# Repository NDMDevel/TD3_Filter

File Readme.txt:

*************************
***** Carpeta DOCs: *****

Contiene documentacion variada, incluyendo manuales de referencia,
PCB del DAC (proyecto de Eagle) y scripts de MATLAB para diseño de
filtros y conversiones de formatos Q15.

**************************
***** Sitios utiles: *****

1- MPLAB X IDE: http://www.microchip.com/mplab/mplab-x-ide

	-> Link directo al instalador (ultima version):
	http://www.microchip.com/mplabx-ide-windows-installer
	
2- Compilador XC16: http://www.microchip.com/mplab/compilers
	
	-> Link directo al instalador de XC16 (ultima version):
	http://www.microchip.com/mplabxc16windows

3- MCC plugin: http://www.microchip.com/mplab/mplab-code-configurator

	-> Instalacion desde MPLAB X.
	
	En MPLAB X ir a: Tools->Plugins->Available Plugins. En el cuadro "Search" buscar "MCC"
	y una vez ubicado tildar el recuadro "install", luego clic en el boton "Install" (abajo a la izq.)

4- dsPIC33EP128GP502 documentacion: 
*Nota: la documentacion de modulos internos del micro (perifericos) estan abajo en la solapa "Documents", seccion "Reference Manual".

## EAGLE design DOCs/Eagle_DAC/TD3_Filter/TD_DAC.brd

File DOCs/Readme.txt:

Sitios utiles:

1- MPLAB X IDE: http://www.microchip.com/mplab/mplab-x-ide

	-> Link directo al instalador (ultima version):
	http://www.microchip.com/mplabx-ide-windows-installer
	
2- Compilador XC16: http://www.microchip.com/mplab/compilers
	
	-> Link directo al instalador de XC16 (ultima version):
	http://www.microchip.com/mplabxc16windows

3- MCC plugin: http://www.microchip.com/mplab/mplab-code-configurator

	-> Instalacion desde MPLAB X.
	
	En MPLAB X ir a: Tools->Plugins->Available Plugins. En el cuadro "Search" buscar "MCC"
	y una vez ubicado tildar el recuadro "install", luego clic en el boton "Install" (abajo a la izq.)

4- dsPIC33EP128GP502 documentacion: 
*Nota: la documentacion de modulos internos del micro (perifericos) estan abajo en la solapa "Documents", seccion "Reference Manual".

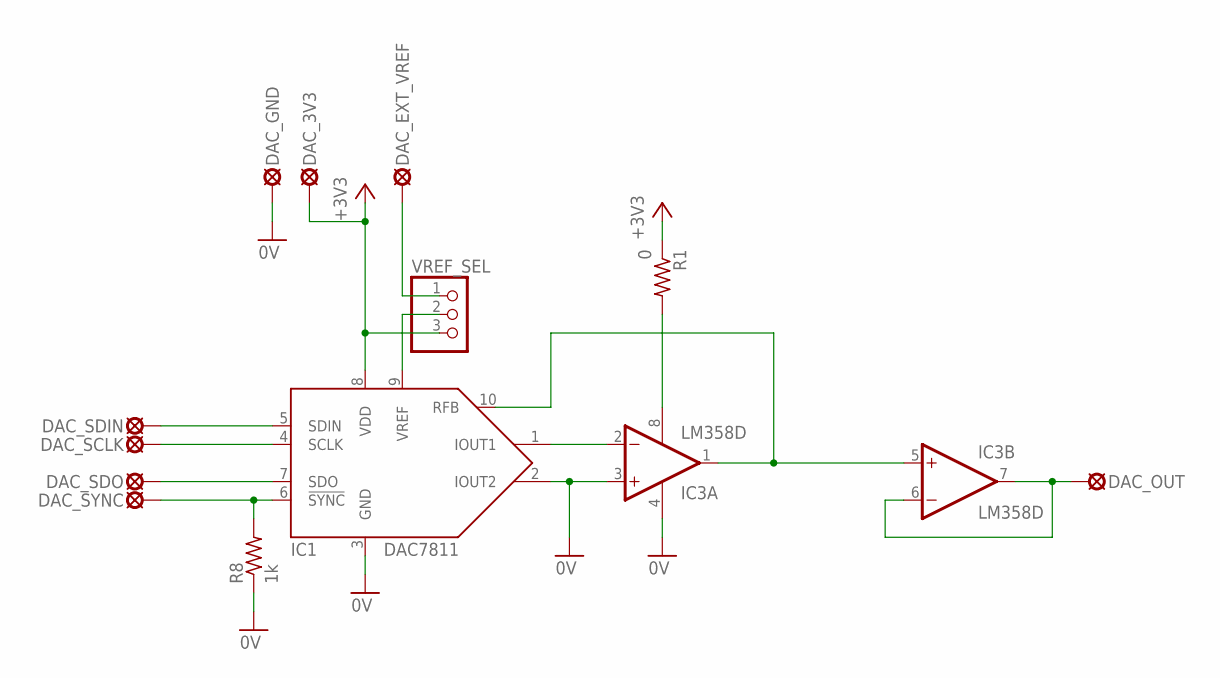
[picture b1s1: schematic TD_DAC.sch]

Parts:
DAC_3V3: LSP10
DAC_EXT_VREF: LSP10
DAC_GND: LSP10
DAC_OUT: LSP10
DAC_SCLK: LSP10
DAC_SDIN: LSP10
DAC_SDO: LSP10
DAC_SYNC: LSP10
IC1: DAC7811; S-PDSO-G10
IC3: LM358D; SO08
R1: 0; R1206
R8: 1k; R0805
VREF_SEL: PINHD-1X3; 1X03

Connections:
0V: DAC_GND.MP, IC1.2 (IOUT2), IC1.3 (GND), IC3.3 (+IN), IC3.4 (V-), R8.1
+3V3: DAC_3V3.MP, IC1.8 (VDD), R1.1, VREF_SEL.3
MCU_SCLK: DAC_SCLK.MP, IC1.4 (SCLK)
MCU_SDO: DAC_SDIN.MP, IC1.5 (SDIN)
unnamed: IC1.1 (IOUT1), IC3.2 (-IN)
unnamed: DAC_OUT.MP, IC3.6 (-IN), IC3.7 (OUT)
unnamed: IC1.9 (VREF), VREF_SEL.2
unnamed: DAC_EXT_VREF.MP, VREF_SEL.1
unnamed: DAC_SYNC.MP, IC1.6 (!SYNC!), R8.2
unnamed: IC1.10 (RFB), IC3.1 (OUT), IC3.5 (+IN)
unnamed: IC3.8 (V+), R1.2
unnamed: DAC_SDO.MP, IC1.7 (SDO)

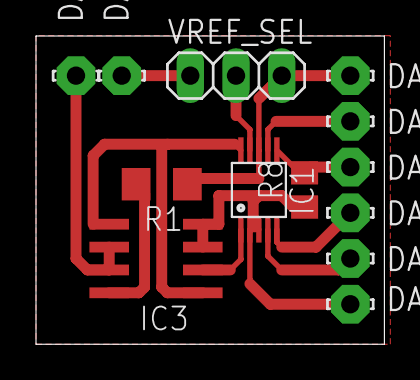
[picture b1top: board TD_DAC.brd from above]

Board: 2 copper layers, 19.4 x 17.1 mm, 13 parts (0 on the bottom side), 12 nets.

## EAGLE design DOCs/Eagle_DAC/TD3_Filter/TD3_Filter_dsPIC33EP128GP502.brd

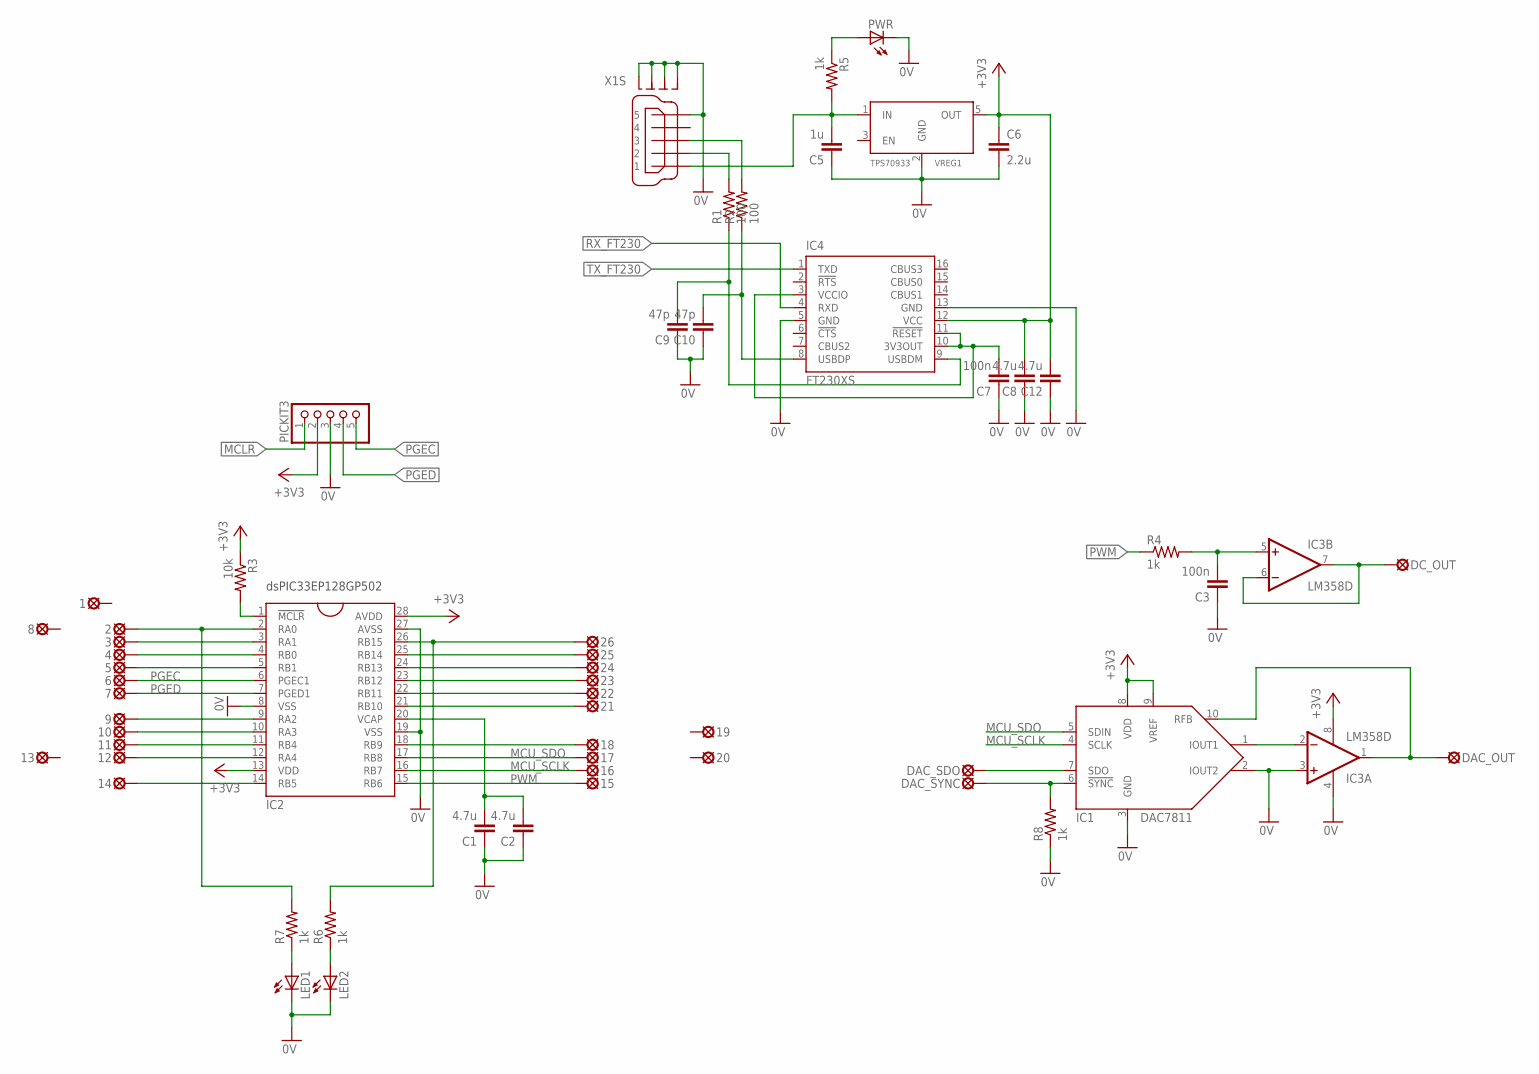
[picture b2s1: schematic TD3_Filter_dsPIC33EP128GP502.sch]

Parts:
1, 2, 3, 4, 5, 6, 7, 8, 9, 10, 11, 12, 13, 14, 15, 16, 17, 18, 19, 20, 21, 22, 23, 24, 25, 26: LSP10
C1, C2, C8, C12: 4.7u; C1206
C3, C7: 100n; C1206
C5: 1u; C1206
C6: 2.2u; C1206
C9, C10: 47p; C1206
DAC_OUT: LSP10
DAC_SDO: LSP10
DAC_SYNC: LSP10
DC_OUT: LSP10
IC1: DAC7811; S-PDSO-G10
IC2: DSPIC33EP128GP502; DIL28
IC3: LM358D; SO08
IC4: FT230XS; SSOP16
LED1, LED2: LED3MM
PICKIT3: PINHD-1X5; 1X05
PWR: LED3MM
R1: 100; R0805
R2: 100; R1206
R3: 10k; R0805
R4, R5, R6, R7, R8: 1k; R0805
VREG1: TPS70933
X1: MINI-USB_SHIELD5P4-32005-400; 32005-400

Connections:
0V: C1.1, C2.1, C3.1, C5.1, C6.2, C7.1, C8.1, C9.1, C10.1, C12.1, IC1.2 (IOUT2), IC1.3 (GND), IC2.8 (VSS), IC2.19 (VSS), IC2.27 (AVSS), IC3.3 (+IN), IC3.4 (V-), IC4.5 (GND), IC4.13 (GND), LED1.K (C), LED2.K (C), PICKIT3.3, PWR.K (C), R8.1, VREG1.2 (GND), X1.5, X1.M1 (S1), X1.M2 (S2), X1.M3 (S3), X1.M4 (S4)
!MCLR!: PICKIT3.1
+3V3: C6.1, C8.2, C12.2, IC1.8 (VDD), IC1.9 (VREF), IC2.13 (VDD), IC2.28 (AVDD), IC3.8 (V+), IC4.12 (VCC), PICKIT3.2, R3.1, VREG1.5 (OUT)
MCU_SCLK: 16.MP, IC1.4 (SCLK), IC2.16 (RB7)
MCU_SDO: 17.MP, IC1.5 (SDIN), IC2.17 (RB8)
unnamed: IC1.1 (IOUT1), IC3.2 (-IN)
unnamed: C3.2, IC3.5 (+IN), R4.2
unnamed: PWR.A, R5.1
unnamed: IC2.1 (!MCLR!), R3.2
unnamed: DAC_SYNC.MP, IC1.6 (!SYNC!), R8.2
unnamed: C7.2, IC4.3 (VCCIO), IC4.10 (3V3OUT), IC4.11 (!RESET)
unnamed: R2.2, X1.3
unnamed: C1.2, C2.2, IC2.20 (VCAP)
unnamed: DAC_SDO.MP, IC1.7 (SDO)
unnamed: C10.2, IC4.8 (USBDP), R2.1
unnamed: R1.2, X1.2
unnamed: C9.2, IC4.9 (USBDM), R1.1
unnamed: DAC_OUT.MP, IC1.10 (RFB), IC3.1 (OUT)
unnamed: DC_OUT.MP, IC3.6 (-IN), IC3.7 (OUT)
unnamed: 3.MP, IC2.3 (RA1)
unnamed: 4.MP, IC2.4 (RB0)
unnamed: 5.MP, IC2.5 (RB1)
unnamed: 9.MP, IC2.9 (RA2)
unnamed: 10.MP, IC2.10 (RA3)
unnamed: 11.MP, IC2.11 (RB4)
unnamed: 12.MP, IC2.12 (RA4)
unnamed: 14.MP, IC2.14 (RB5)
unnamed: 22.MP, IC2.22 (RB11)
unnamed: 18.MP, IC2.18 (RB9)
unnamed: 21.MP, IC2.21 (RB10)
unnamed: 23.MP, IC2.23 (RB12)
unnamed: 24.MP, IC2.24 (RB13)
unnamed: 25.MP, IC2.25 (RB14)
unnamed: LED2.A, R6.1
unnamed: LED1.A, R7.1
unnamed: 2.MP, IC2.2 (RA0), R7.2
unnamed: C5.2, R5.2, VREG1.1 (IN), X1.1
unnamed: 26.MP, IC2.26 (RB15), R6.2
PGEC: 6.MP, IC2.6 (PGEC1), PICKIT3.5
PGED: 7.MP, IC2.7 (PGED1), PICKIT3.4
PWM: 15.MP, IC2.15 (RB6), R4.1
RX_FT230: IC4.4 (RXD)
TX_FT230: IC4.1 (TXD)

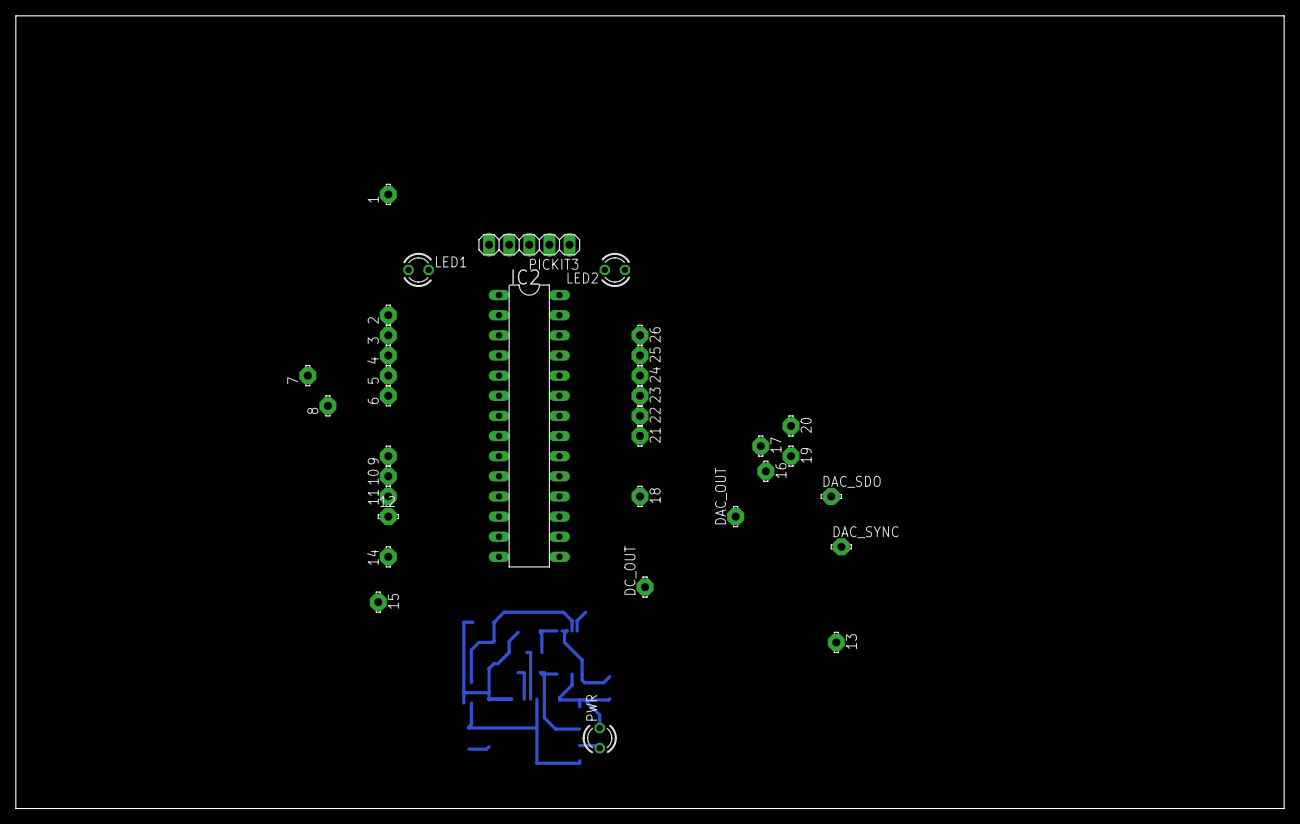
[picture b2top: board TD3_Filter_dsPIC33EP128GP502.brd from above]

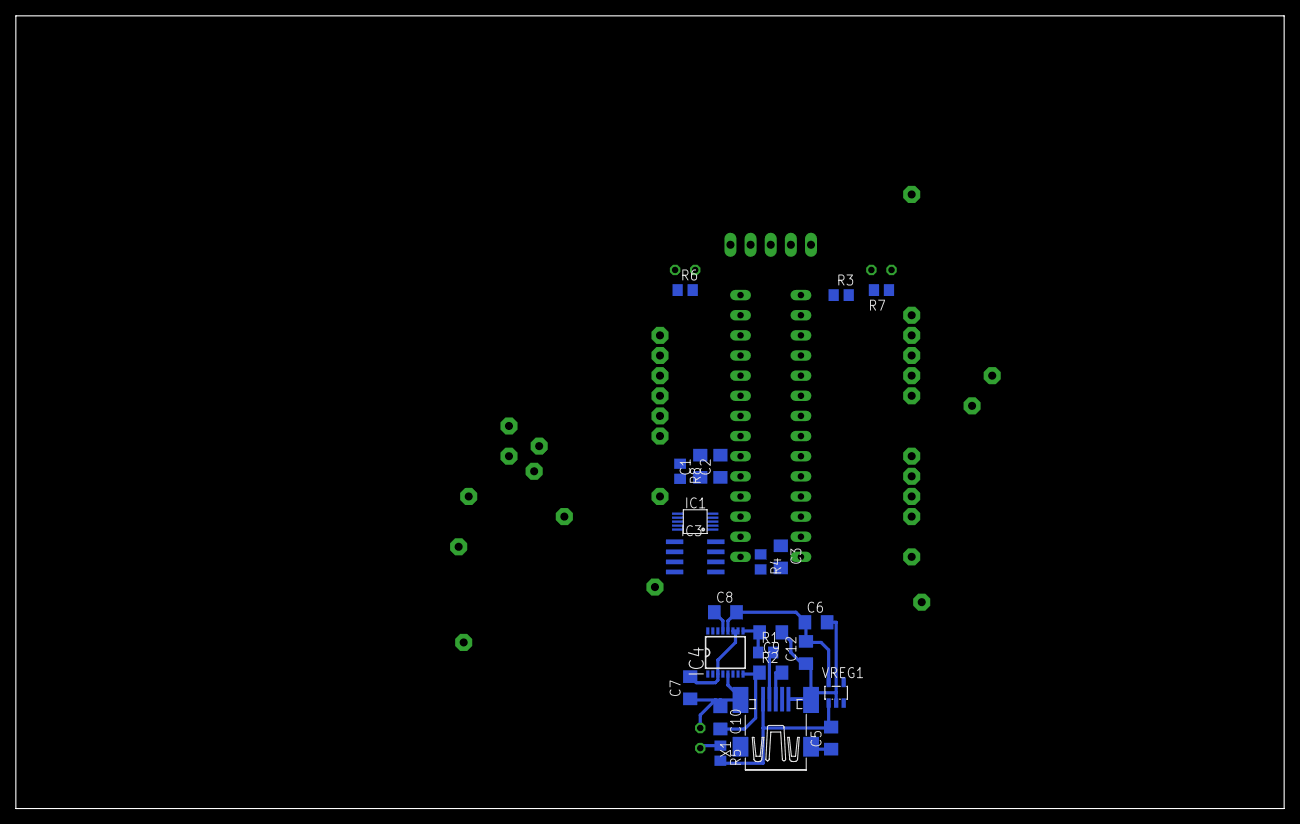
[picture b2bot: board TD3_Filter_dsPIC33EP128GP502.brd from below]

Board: 2 copper layers, 160.0 x 100.0 mm, 58 parts (23 on the bottom side), 40 nets.

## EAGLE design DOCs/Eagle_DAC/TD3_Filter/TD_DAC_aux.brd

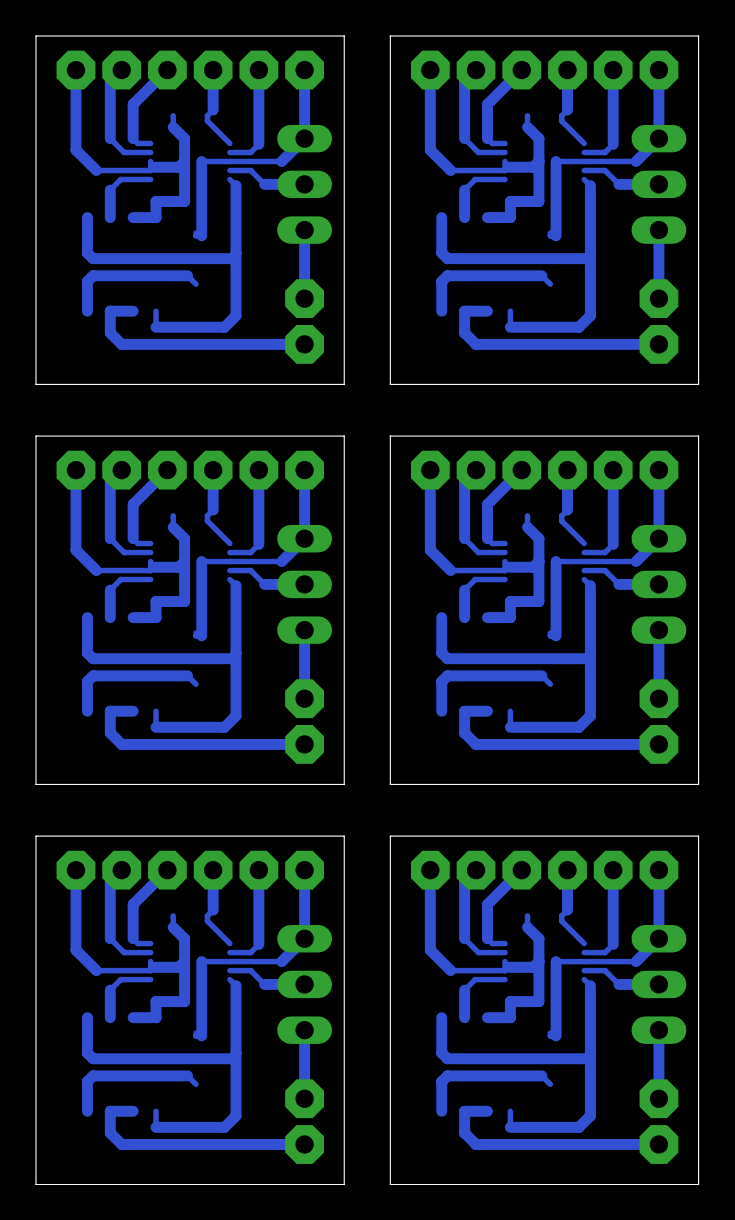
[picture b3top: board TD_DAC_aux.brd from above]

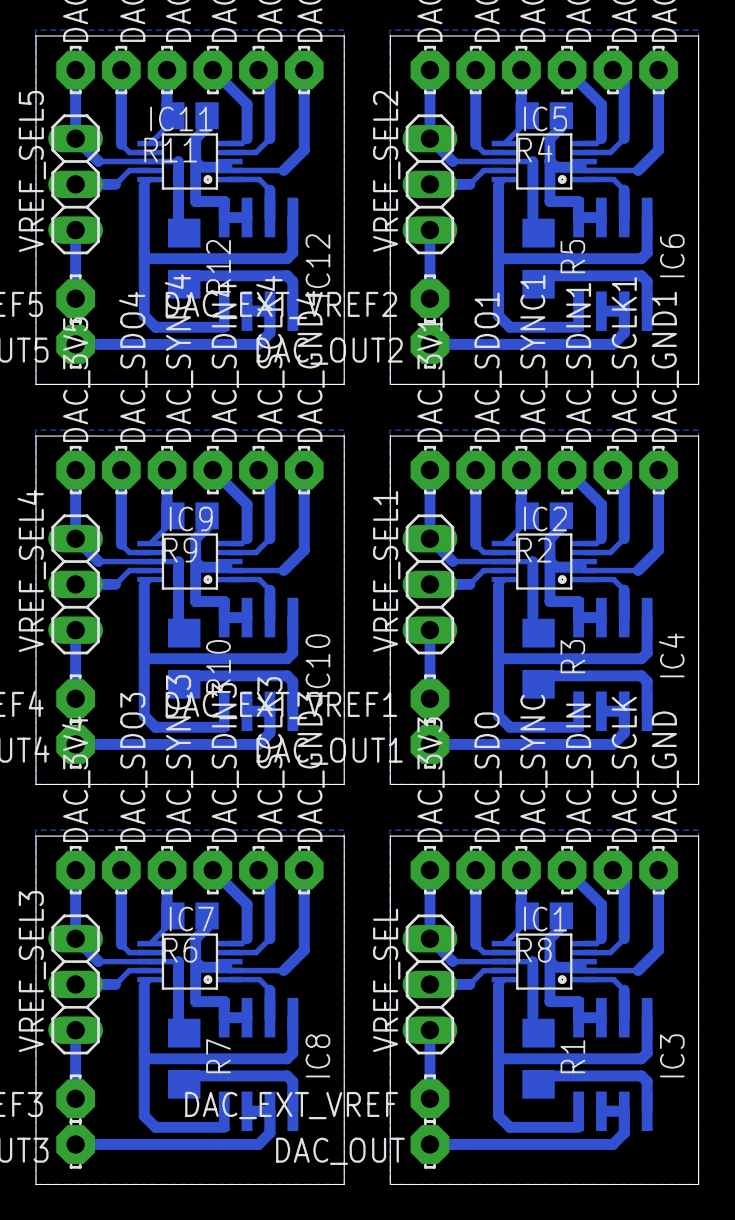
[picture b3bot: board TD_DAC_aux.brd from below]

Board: 2 copper layers, 36.8 x 63.8 mm, 78 parts (78 on the bottom side), 72 nets.

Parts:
DAC_3V1, DAC_3V2, DAC_3V3, DAC_3V4, DAC_3V5, DAC_3V6: LSP10
DAC_EXT_VREF, DAC_EXT_VREF1, DAC_EXT_VREF2, DAC_EXT_VREF3, DAC_EXT_VREF4, DAC_EXT_VREF5: LSP10
DAC_GND, DAC_GND1, DAC_GND2, DAC_GND3, DAC_GND4, DAC_GND5: LSP10
DAC_OUT, DAC_OUT1, DAC_OUT2, DAC_OUT3, DAC_OUT4, DAC_OUT5: LSP10
DAC_SCLK, DAC_SCLK1, DAC_SCLK2, DAC_SCLK3, DAC_SCLK4, DAC_SCLK5: LSP10
DAC_SDIN, DAC_SDIN1, DAC_SDIN2, DAC_SDIN3, DAC_SDIN4, DAC_SDIN5: LSP10
DAC_SDO, DAC_SDO1, DAC_SDO2, DAC_SDO3, DAC_SDO4, DAC_SDO5: LSP10
DAC_SYNC, DAC_SYNC1, DAC_SYNC2, DAC_SYNC3, DAC_SYNC4, DAC_SYNC5: LSP10
IC1, IC2, IC5, IC7, IC9, IC11: S-PDSO-G10
IC3, IC4, IC6, IC8, IC10, IC12: LM358D; SO08
R1, R3, R5, R7, R10, R12: 0; R1206
R2, R4, R6, R8, R9, R11: 1k; R0805
VREF_SEL, VREF_SEL1, VREF_SEL2, VREF_SEL3, VREF_SEL4, VREF_SEL5: 1X03

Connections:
0V: DAC_GND.MP, IC1.2, IC1.3, IC3.3, IC3.4, R8.1
0V1: DAC_GND1.MP, IC2.2, IC2.3, IC4.3, IC4.4, R2.1
0V2: DAC_GND2.MP, IC5.2, IC5.3, IC6.3, IC6.4, R4.1
0V3: DAC_GND3.MP, IC7.2, IC7.3, IC8.3, IC8.4, R6.1
0V4: DAC_GND4.MP, IC9.2, IC9.3, IC10.3, IC10.4, R9.1
0V5: DAC_GND5.MP, IC11.2, IC11.3, IC12.3, IC12.4, R11.1
+3V1: DAC_3V1.MP, IC2.8, R3.1, VREF_SEL1.3
+3V2: DAC_3V2.MP, IC5.8, R5.1, VREF_SEL2.3
+3V3: DAC_3V3.MP, IC1.8, R1.1, VREF_SEL.3
+3V4: DAC_3V4.MP, IC7.8, R7.1, VREF_SEL3.3
+3V5: DAC_3V5.MP, IC9.8, R10.1, VREF_SEL4.3
+3V6: DAC_3V6.MP, IC11.8, R12.1, VREF_SEL5.3
MCU_SCLK: DAC_SCLK.MP, IC1.4
MCU_SCLK1: DAC_SCLK1.MP, IC2.4
MCU_SCLK2: DAC_SCLK2.MP, IC5.4
MCU_SCLK3: DAC_SCLK3.MP, IC7.4
MCU_SCLK4: DAC_SCLK4.MP, IC9.4
MCU_SCLK5: DAC_SCLK5.MP, IC11.4
MCU_SDO: DAC_SDIN.MP, IC1.5
MCU_SDO1: DAC_SDIN1.MP, IC2.5
MCU_SDO2: DAC_SDIN2.MP, IC5.5
MCU_SDO3: DAC_SDIN3.MP, IC7.5
MCU_SDO4: DAC_SDIN4.MP, IC9.5
MCU_SDO5: DAC_SDIN5.MP, IC11.5
unnamed: IC1.1, IC3.2
unnamed: DAC_OUT.MP, IC3.6, IC3.7
unnamed: IC1.9, VREF_SEL.2
unnamed: DAC_EXT_VREF.MP, VREF_SEL.1
unnamed: DAC_SYNC.MP, IC1.6, R8.2
unnamed: IC1.10, IC3.1, IC3.5
unnamed: IC3.8, R1.2
unnamed: IC2.1, IC4.2
unnamed: DAC_SDO.MP, IC1.7
unnamed: DAC_SYNC1.MP, IC2.6, R2.2
unnamed: DAC_SDO1.MP, IC2.7
unnamed: DAC_OUT1.MP, IC4.6, IC4.7
unnamed: IC2.9, VREF_SEL1.2
unnamed: DAC_EXT_VREF1.MP, VREF_SEL1.1
unnamed: IC2.10, IC4.1, IC4.5
unnamed: IC4.8, R3.2
unnamed: IC5.1, IC6.2
unnamed: DAC_SYNC2.MP, IC5.6, R4.2
unnamed: DAC_SDO2.MP, IC5.7
unnamed: DAC_OUT2.MP, IC6.6, IC6.7
unnamed: IC5.9, VREF_SEL2.2
unnamed: DAC_EXT_VREF2.MP, VREF_SEL2.1
unnamed: IC5.10, IC6.1, IC6.5
unnamed: IC6.8, R5.2
unnamed: IC7.1, IC8.2
unnamed: DAC_SYNC3.MP, IC7.6, R6.2
unnamed: DAC_SDO3.MP, IC7.7
unnamed: DAC_OUT3.MP, IC8.6, IC8.7
unnamed: IC7.9, VREF_SEL3.2
unnamed: DAC_EXT_VREF3.MP, VREF_SEL3.1
unnamed: IC7.10, IC8.1, IC8.5
unnamed: IC8.8, R7.2
unnamed: IC9.1, IC10.2
unnamed: DAC_SYNC4.MP, IC9.6, R9.2
unnamed: DAC_SDO4.MP, IC9.7
unnamed: DAC_OUT4.MP, IC10.6, IC10.7
unnamed: IC9.9, VREF_SEL4.2
unnamed: DAC_EXT_VREF4.MP, VREF_SEL4.1
unnamed: IC9.10, IC10.1, IC10.5
unnamed: IC10.8, R10.2
unnamed: IC11.1, IC12.2
unnamed: DAC_SYNC5.MP, IC11.6, R11.2
unnamed: DAC_SDO5.MP, IC11.7
unnamed: DAC_OUT5.MP, IC12.6, IC12.7
unnamed: IC11.9, VREF_SEL5.2
unnamed: DAC_EXT_VREF5.MP, VREF_SEL5.1
unnamed: IC11.10, IC12.1, IC12.5
unnamed: IC12.8, R12.2

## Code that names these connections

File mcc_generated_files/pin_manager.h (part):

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*/
/**
  @Summary
    Sets the GPIO pin, RA0, high using LATA0.

  @Description
    Sets the GPIO pin, RA0, high using LATA0.

  @Preconditions
    The RA0 must be set to an output.
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#define channel_AN0_SetHigh()          _LATA0 = 1
/**
  @Summary
    Sets the GPIO pin, RA0, low using LATA0.

  @Description
    Sets the GPIO pin, RA0, low using LATA0.

  @Preconditions
    The RA0 must be set to an output.
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#define channel_AN0_SetLow()           _LATA0 = 0
/**
  @Summary
    Toggles the GPIO pin, RA0, using LATA0.

  @Description
    Toggles the GPIO pin, RA0, using LATA0.

  @Preconditions
    The RA0 must be set to an output.
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#define channel_AN0_Toggle()           _LATA0 ^= 1
/**
  @Summary
    Reads the value of the GPIO pin, RA0.

  @Description
    Reads the value of the GPIO pin, RA0.

  @Preconditions
    None.
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    </code>

*/
#define channel_AN0_GetValue()         _RA0
/**
  @Summary
    Configures the GPIO pin, RA0, as an input.

  @Description
    Configures the GPIO pin, RA0, as an input.

  @Preconditions
    None.
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#define channel_AN0_SetDigitalInput()  _TRISA0 = 1
/**
  @Summary
    Configures the GPIO pin, RA0, as an output.

  @Description
    Configures the GPIO pin, RA0, as an output.

  @Preconditions
    None.
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#define channel_AN0_SetDigitalOutput() _TRISA0 = 0
/**
  @Summary
    Sets the GPIO pin, RB0, high using LATB0.

  @Description
    Sets the GPIO pin, RB0, high using LATB0.

  @Preconditions
    The RB0 must be set to an output.
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#define SS1_SetHigh()          _LATB0 = 1
/**
  @Summary
    Sets the GPIO pin, RB0, low using LATB0.

  @Description
    Sets the GPIO pin, RB0, low using LATB0.

  @Preconditions
    The RB0 must be set to an output.
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#define SS1_SetLow()           _LATB0 = 0
/**
  @Summary
    Toggles the GPIO pin, RB0, using LATB0.

  @Description
    Toggles the GPIO pin, RB0, using LATB0.

  @Preconditions
    The RB0 must be set to an output.
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#define SS1_Toggle()           _LATB0 ^= 1
/**
  @Summary
    Reads the value of the GPIO pin, RB0.

  @Description
    Reads the value of the GPIO pin, RB0.

  @Preconditions
    None.
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    </code>

*/
#define SS1_GetValue()         _RB0
/**
  @Summary
    Configures the GPIO pin, RB0, as an input.

  @Description
    Configures the GPIO pin, RB0, as an input.

  @Preconditions
    None.
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#define SS1_SetDigitalInput()  _TRISB0 = 1
/**
  @Summary
    Configures the GPIO pin, RB0, as an output.

  @Description
    Configures the GPIO pin, RB0, as an output.

  @Preconditions
    None.
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#define SS1_SetDigitalOutput() _TRISB0 = 0
/**
  @Summary
    Sets the GPIO pin, RB6, high using LATB6.

  @Description
    Sets the GPIO pin, RB6, high using LATB6.

  @Preconditions
    The RB6 must be set to an output.
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#define IO_RB6_SetHigh()          _LATB6 = 1
/**
  @Summary
    Sets the GPIO pin, RB6, low using LATB6.

  @Description
    Sets the GPIO pin, RB6, low using LATB6.

  @Preconditions
    The RB6 must be set to an output.
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#define IO_RB6_SetLow()           _LATB6 = 0
/**
  @Summary
    Toggles the GPIO pin, RB6, using LATB6.

  @Description
    Toggles the GPIO pin, RB6, using LATB6.

  @Preconditions
    The RB6 must be set to an output.
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#define IO_RB6_Toggle()           _LATB6 ^= 1
/**
  @Summary
    Reads the value of the GPIO pin, RB6.

  @Description
    Reads the value of the GPIO pin, RB6.

  @Preconditions
    None.
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    </code>

*/
#define IO_RB6_GetValue()         _RB6
/**
  @Summary
    Configures the GPIO pin, RB6, as an input.

  @Description
    Configures the GPIO pin, RB6, as an input.

  @Preconditions
    None.
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#define IO_RB6_SetDigitalInput()  _TRISB6 = 1
/**
  @Summary
    Configures the GPIO pin, RB6, as an output.

  @Description
    Configures the GPIO pin, RB6, as an output.

  @Preconditions
    None.
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#define IO_RB6_SetDigitalOutput() _TRISB6 = 0
/**
  @Summary
    Sets the GPIO pin, RB7, high using LATB7.

  @Description
    Sets the GPIO pin, RB7, high using LATB7.

  @Preconditions
    The RB7 must be set to an output.
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#define SCK1_SetHigh()          _LATB7 = 1
/**
  @Summary
    Sets the GPIO pin, RB7, low using LATB7.

  @Description
    Sets the GPIO pin, RB7, low using LATB7.

  @Preconditions
    The RB7 must be set to an output.
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#define SCK1_SetLow()           _LATB7 = 0
/**
  @Summary
    Toggles the GPIO pin, RB7, using LATB7.

  @Description
    Toggles the GPIO pin, RB7, using LATB7.

  @Preconditions
    The RB7 must be set to an output.
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#define SCK1_Toggle()           _LATB7 ^= 1
/**
  @Summary
    Reads the value of the GPIO pin, RB7.

  @Description
    Reads the value of the GPIO pin, RB7.

  @Preconditions
    None.
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    </code>

*/
#define SCK1_GetValue()         _RB7
/**
  @Summary
    Configures the GPIO pin, RB7, as an input.

  @Description
    Configures the GPIO pin, RB7, as an input.

  @Preconditions
    None.
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#define SCK1_SetDigitalInput()  _TRISB7 = 1
/**
  @Summary
    Configures the GPIO pin, RB7, as an output.

  @Description
    Configures the GPIO pin, RB7, as an output.

  @Preconditions
    None.
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#define SCK1_SetDigitalOutput() _TRISB7 = 0
/**
  @Summary
    Sets the GPIO pin, RB8, high using LATB8.

  @Description
    Sets the GPIO pin, RB8, high using LATB8.

  @Preconditions
    The RB8 must be set to an output.
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#define SDO1_SetHigh()          _LATB8 = 1
/**
  @Summary
    Sets the GPIO pin, RB8, low using LATB8.

  @Description
    Sets the GPIO pin, RB8, low using LATB8.

  @Preconditions
    The RB8 must be set to an output.
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#define SDO1_SetLow()           _LATB8 = 0
/**
  @Summary
    Toggles the GPIO pin, RB8, using LATB8.

  @Description
    Toggles the GPIO pin, RB8, using LATB8.

  @Preconditions
    The RB8 must be set to an output.
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#define SDO1_Toggle()           _LATB8 ^= 1
/**
  @Summary
    Reads the value of the GPIO pin, RB8.

  @Description
    Reads the value of the GPIO pin, RB8.

  @Preconditions
    None.
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    </code>

*/
#define SDO1_GetValue()         _RB8
/**
  @Summary
    Configures the GPIO pin, RB8, as an input.

  @Description
    Configures the GPIO pin, RB8, as an input.

  @Preconditions
    None.
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#define SDO1_SetDigitalInput()  _TRISB8 = 1
/**
  @Summary
    Configures the GPIO pin, RB8, as an output.

  @Description
    Configures the GPIO pin, RB8, as an output.

  @Preconditions
    None.
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#define SDO1_SetDigitalOutput() _TRISB8 = 0
/**
  @Summary
    Sets the GPIO pin, RB9, high using LATB9.

  @Description
    Sets the GPIO pin, RB9, high using LATB9.

  @Preconditions
    The RB9 must be set to an output.
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#define SDI1_SetHigh()          _LATB9 = 1
/**
  @Summary
    Sets the GPIO pin, RB9, low using LATB9.

  @Description
    Sets the GPIO pin, RB9, low using LATB9.

  @Preconditions
    The RB9 must be set to an output.
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#define SDI1_SetLow()           _LATB9 = 0
/**
  @Summary
    Toggles the GPIO pin, RB9, using LATB9.

  @Description
    Toggles the GPIO pin, RB9, using LATB9.

  @Preconditions
    The RB9 must be set to an output.
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#define SDI1_Toggle()           _LATB9 ^= 1
/**
  @Summary
    Reads the value of the GPIO pin, RB9.

  @Description
    Reads the value of the GPIO pin, RB9.

  @Preconditions
    None.
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    </code>

*/
#define SDI1_GetValue()         _RB9
/**
  @Summary
    Configures the GPIO pin, RB9, as an input.

  @Description
    Configures the GPIO pin, RB9, as an input.

  @Preconditions
    None.
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#define SDI1_SetDigitalInput()  _TRISB9 = 1
/**
  @Summary
    Configures the GPIO pin, RB9, as an output.

  @Description
    Configures the GPIO pin, RB9, as an output.

  @Preconditions
    None.
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
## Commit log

2018-06-05 Filtro FIR.
    TM3 es el trigger del ADC, por SPI se comunica al DAC externo.
2018-06-21 Filtro FIR.
    Se agrega pdf que describe como usar los script de MATLAB para diseñar FIRs y convertirlos a Q15.

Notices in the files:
mcc_generated_files/pin_manager.h:
Copyright (c) 2013 - 2015 released Microchip Technology Inc.  All rights reserved.
